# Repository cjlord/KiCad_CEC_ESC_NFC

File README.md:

# KiCad_CEC_ESC_NFC
Repository for the KiCad class taught on Design News CEC and the ESC NFC tutorial

Expect the KiCad class files to be loaded by about March 10, 2019.

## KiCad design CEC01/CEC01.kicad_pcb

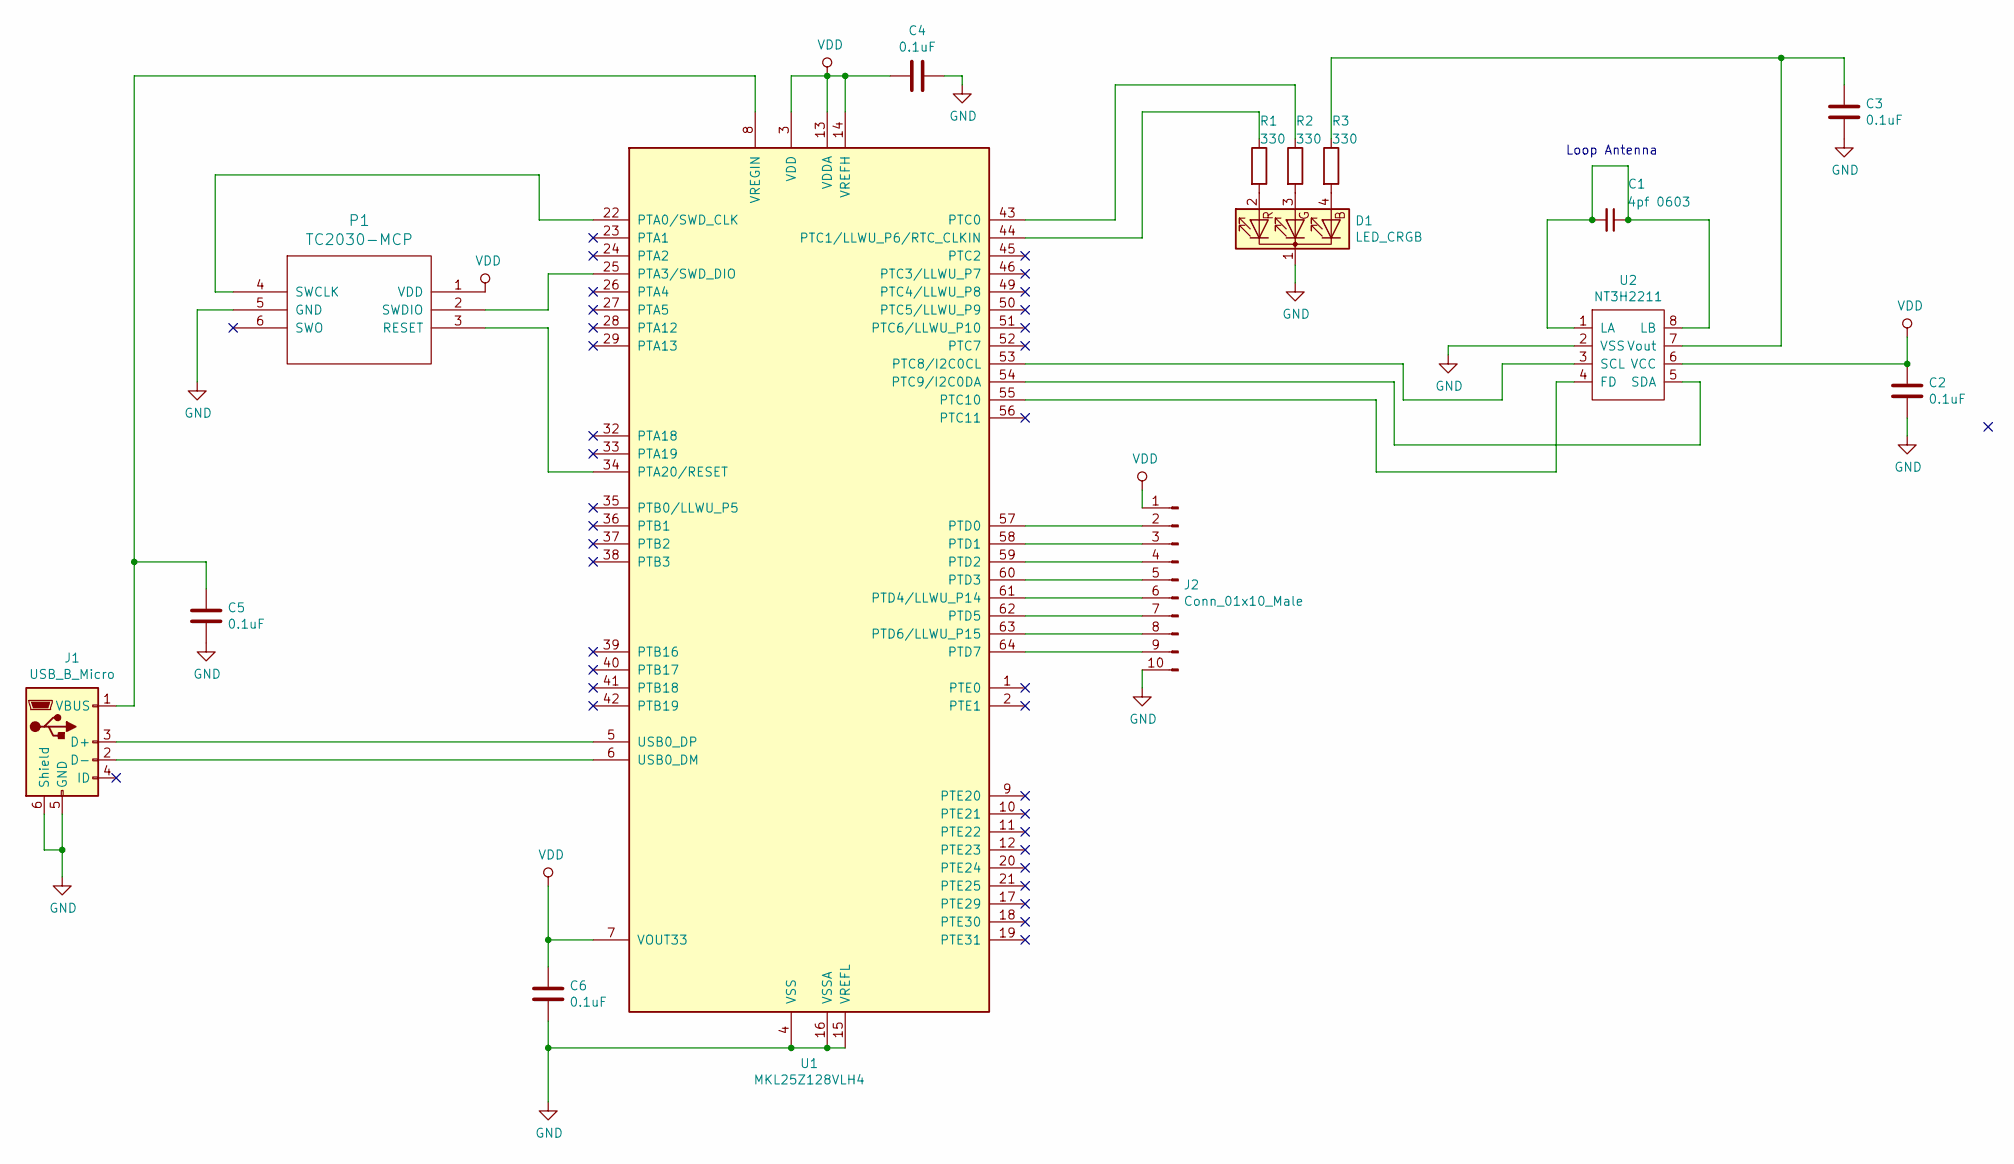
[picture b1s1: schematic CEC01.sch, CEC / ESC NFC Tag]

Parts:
C1: 4pf 0603; C_0603_1608Metric
C2, C3, C4, C5, C6: 0.1uF; C_0603_1608Metric
D1: LED_CRGB; LED_D5.0mm-4_RGB
J1: USB_B_Micro; 10104110-0001LF
J2: Conn_01x10_Male; PinHeader_1x10_P2.54mm_Vertical
P1: TC2030-MCP; Tag-Connect_TC2030-IDC-FP_2x03_P1.27mm_Vertical
R1, R2, R3: 330; R_0603_1608Metric
U1: MKL25Z128VLH4; LQFP-64_10x10mm_P0.5mm
U2: NT3H2211; SO-8_5.3x6.2mm_P1.27mm

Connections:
GND: C2.2, C3.2, C4.1, C5.2, C6.2, D1.1 (K), J1.5 (GND), J1.6 (Shield), J2.10, P1.5 (GND), U1.4 (VSS), U1.15 (VREFL), U1.16 (VSSA), U1.31 (VSS), U1.47 (VSS), U2.2 (VSS)
unnamed: C1.1, C1.2, U2.1 (LA), U2.8 (LB)
unnamed: C3.1, R3.1, U2.7 (Vout)
unnamed: C5.1, J1.1 (VBUS), U1.8 (VREGIN)
unnamed: D1.2 (RA), R1.2
unnamed: D1.3 (GA), R2.2
unnamed: D1.4 (BA), R3.2
unnamed: J1.2 (D-), U1.6 (USB0_DM)
unnamed: J1.3 (D+), U1.5 (USB0_DP)
unnamed: J2.2, U1.57 (PTD0)
unnamed: J2.3, U1.58 (PTD1)
unnamed: J2.4, U1.59 (PTD2)
unnamed: J2.5, U1.60 (PTD3)
unnamed: J2.6, U1.61 (PTD4/LLWU_P14)
unnamed: J2.7, U1.62 (PTD5)
unnamed: J2.8, U1.63 (PTD6/LLWU_P15)
unnamed: J2.9, U1.64 (PTD7)
unnamed: P1.2 (SWDIO), U1.25 (PTA3/SWD_DIO)
unnamed: P1.3 (RESET), U1.34 (PTA20/RESET)
unnamed: P1.4 (SWCLK), U1.22 (PTA0/SWD_CLK)
unnamed: R1.1, U1.44 (PTC1/LLWU_P6/RTC_CLKIN)
unnamed: R2.1, U1.43 (PTC0)
unnamed: U1.53 (PTC8/I2C0CL), U2.3 (SCL)
unnamed: U1.54 (PTC9/I2C0DA), U2.5 (SDA)
unnamed: U1.55 (PTC10), U2.4 (FD)
VDD: C2.1, C4.2, C6.1, J2.1, P1.1 (VDD), U1.3 (VDD), U1.7 (VOUT33), U1.13 (VDDA), U1.14 (VREFH), U1.30 (VDD), U1.48 (VDD), U2.6 (VCC)

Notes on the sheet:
Loop Antenna

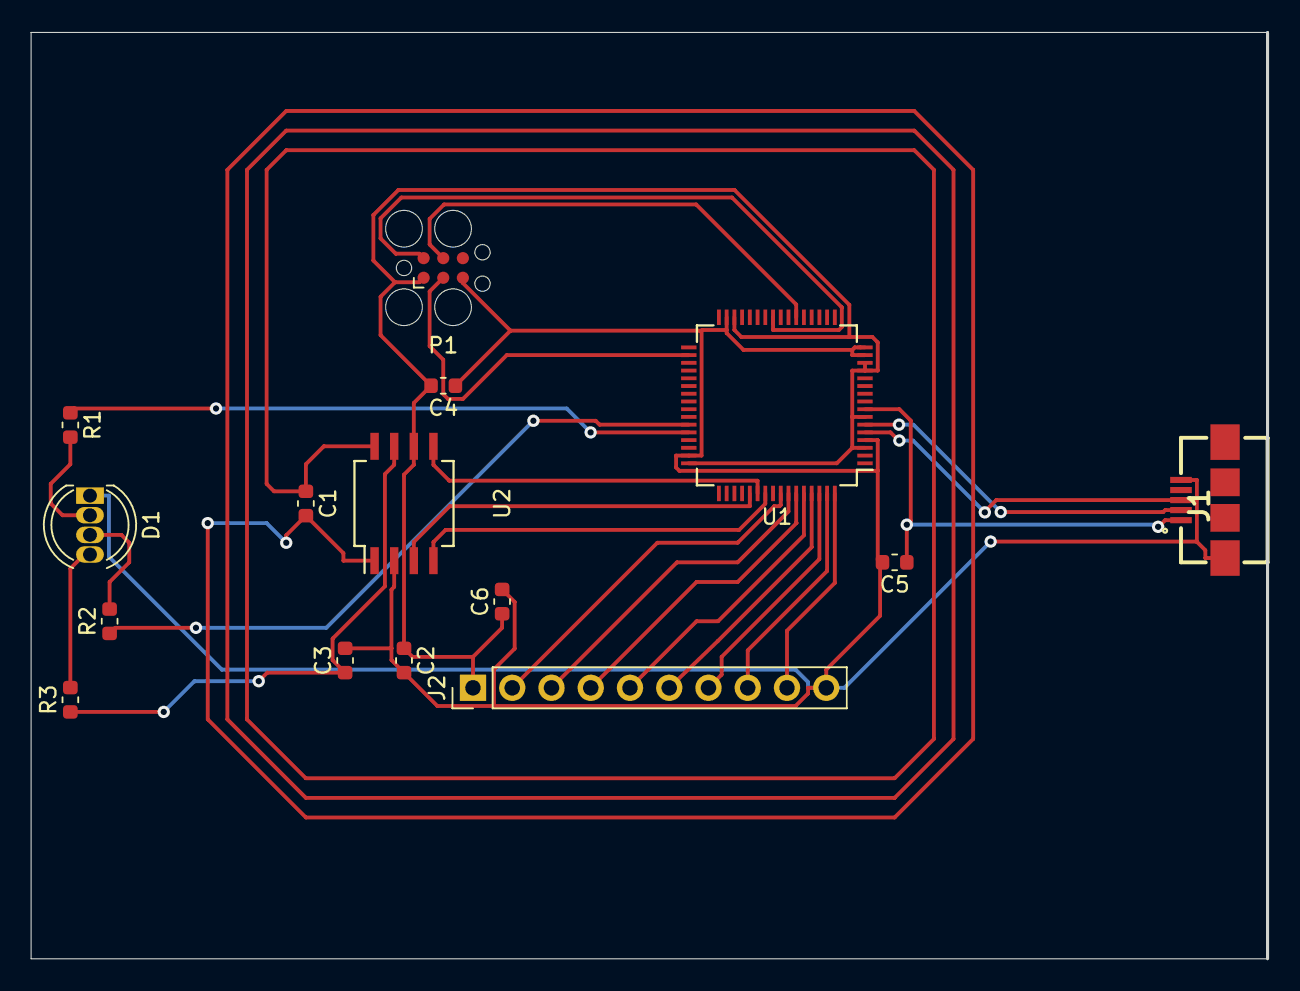
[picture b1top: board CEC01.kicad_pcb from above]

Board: 2 copper layers, 79.9 x 59.9 mm, 15 parts (0 on the bottom side), 26 nets.

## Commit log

2019-03-01 Added all of the CEC files from KiCad
